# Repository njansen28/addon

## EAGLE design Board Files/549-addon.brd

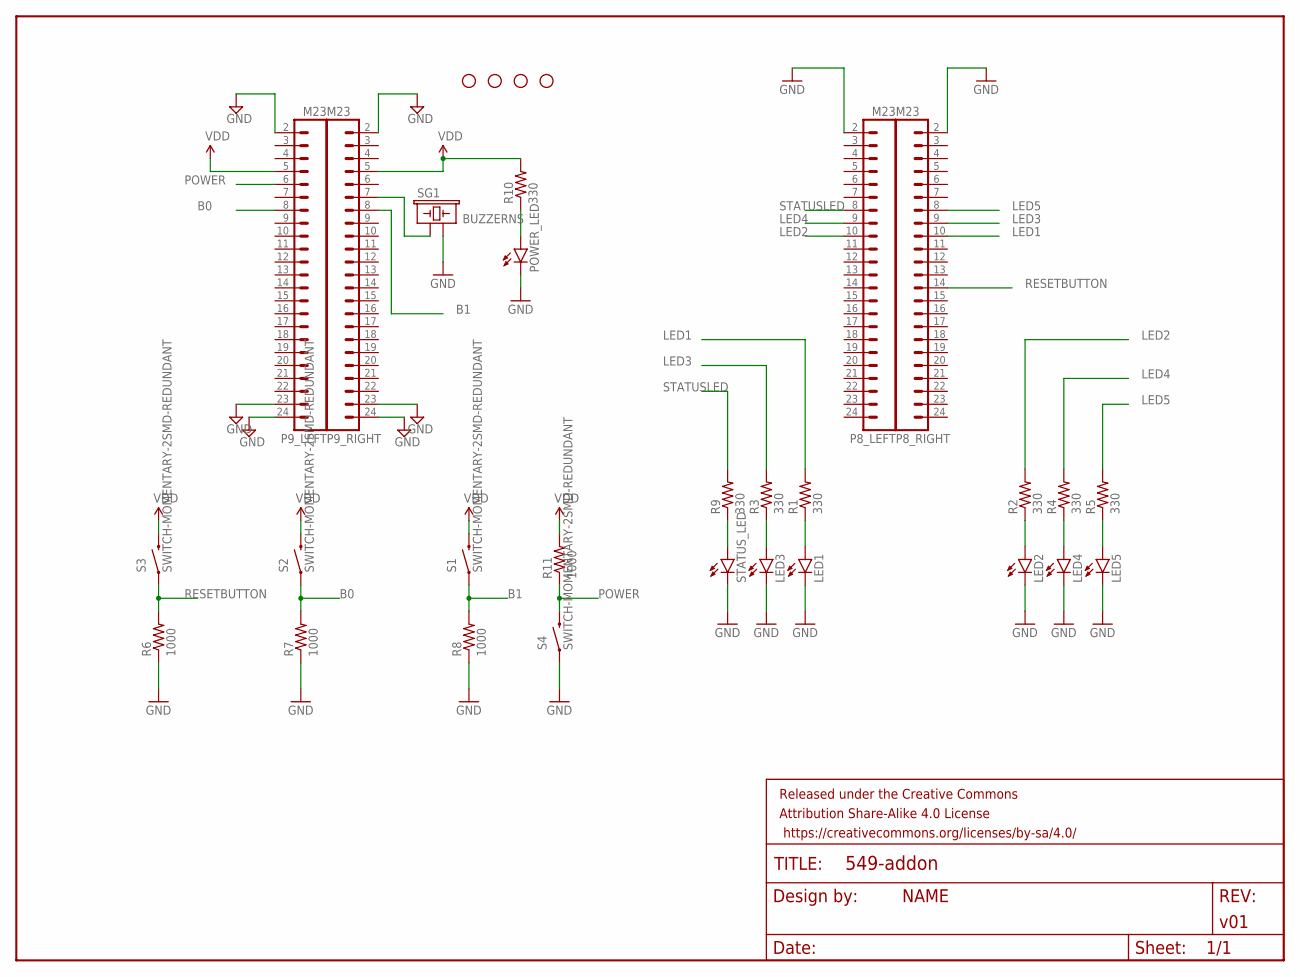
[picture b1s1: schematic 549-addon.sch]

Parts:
FRAME1: FRAME-LETTER; CREATIVE_COMMONS
LED1, LED2, LED3, LED4, LED5: LED1206; LED-1206
P8_LEFT, P8_RIGHT, P9_LEFT, P9_RIGHT: M23; 1X23
POWER_LED: LED1206; LED-1206
R1, R2, R3, R4, R5, R9, R10: 330; 1206
R6, R7, R8, R11: 1000; 1206
S1, S2, S3, S4: SWITCH-MOMENTARY-2SMD-REDUNDANT; TACTILE-SWITCH-SMD
SG1: BUZZERNS; BUZZER-12MM-NS
STANDOFF1, STANDOFF2, STANDOFF3, STANDOFF4: STAND-OFF
STATUS_LED: LED1206; LED-1206

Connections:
B0: P9_LEFT.8, R7.2, S2.1, S2.2 (1)
B1: P9_RIGHT.8, R8.2, S1.1, S1.2 (1)
GND: LED1.C, LED2.C, LED3.C, LED4.C, LED5.C, P8_LEFT.2, P8_RIGHT.2, P9_LEFT.2, P9_LEFT.23, P9_LEFT.24, P9_RIGHT.2, P9_RIGHT.23, P9_RIGHT.24, POWER_LED.C, R6.1, R7.1, R8.1, S4.1, S4.2 (1), SG1.- (2), STATUS_LED.C
LED1: P8_RIGHT.10, R1.2
LED2: P8_LEFT.10, R2.2
LED3: P8_RIGHT.9, R3.2
LED4: P8_LEFT.9, R4.2
LED5: P8_RIGHT.8, R5.2
unnamed: LED1.A, R1.1
unnamed: LED2.A, R2.1
unnamed: LED3.A, R3.1
unnamed: LED4.A, R4.1
unnamed: LED5.A, R5.1
unnamed: R9.1, STATUS_LED.A
unnamed: POWER_LED.A, R10.1
unnamed: P9_RIGHT.7, SG1.+ (1)
POWER: P9_LEFT.6, R11.1, S4.3 (2), S4.4 (2)
RESETBUTTON: P8_RIGHT.14, R6.2, S3.1, S3.2 (1)
STATUSLED: P8_LEFT.8, R9.2
VDD: P9_LEFT.5, P9_RIGHT.5, R10.2, R11.2, S1.3 (2), S1.4 (2), S2.3 (2), S2.4 (2), S3.3 (2), S3.4 (2)

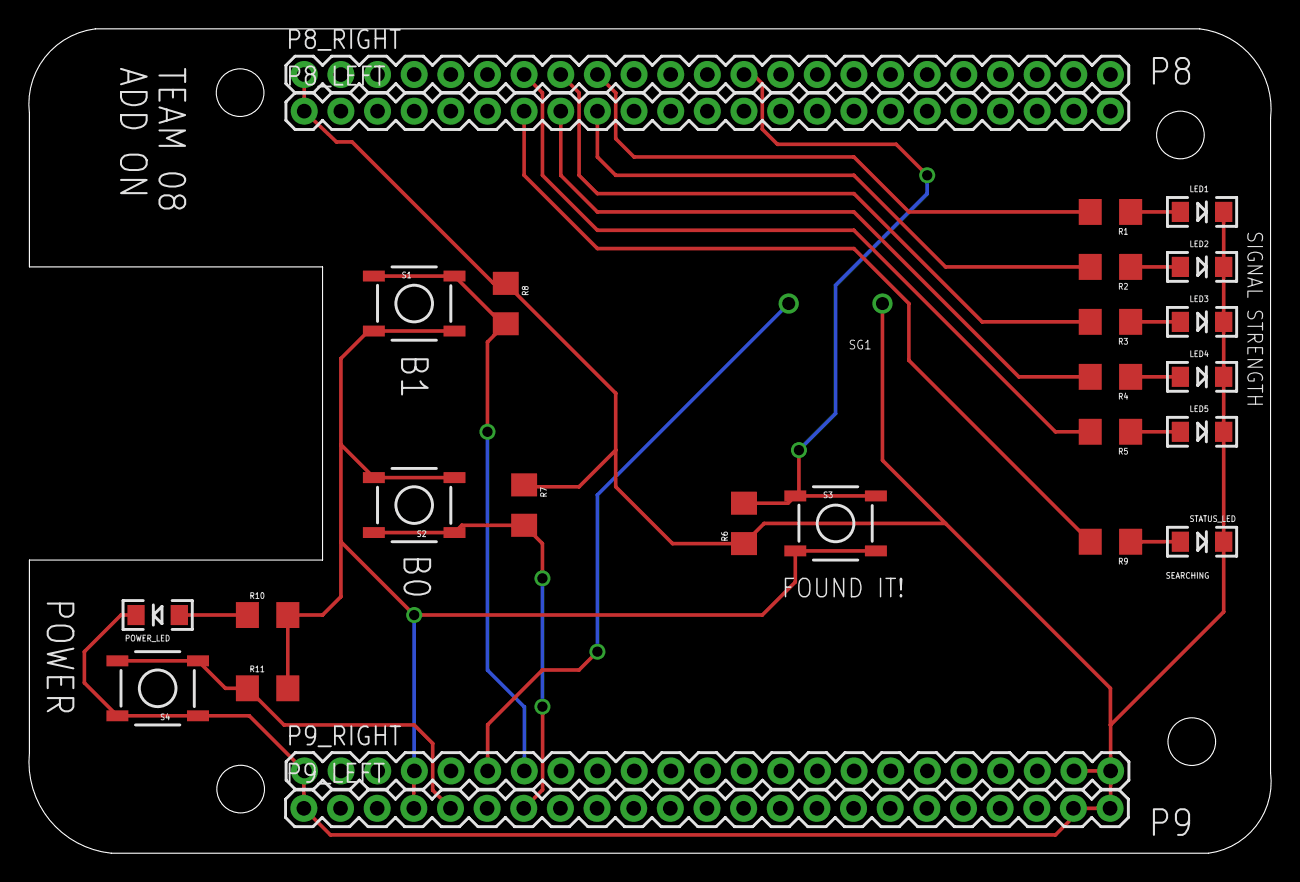
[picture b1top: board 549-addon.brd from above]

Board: 2 copper layers, 86.1 x 57.1 mm, 32 parts (0 on the bottom side), 20 nets.

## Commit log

2015-03-05 Initial commit of addon test code
2015-03-05 Added a folder for better organization
2015-03-16 Compiles, sends init sequence to BLE mini after button press, prints all bytes received from serial port (currently having issues with serial receive)
2015-03-21 brd and sch file for add on pcb. Please look over and make sure I'm not doing anything stupid
2015-03-22 Can you see this Bryan? If so, can you calm down a little bit? heh
2015-03-23 Modified some of Bryan's code to hopefully work for addon
2015-03-23 Fixed formatting for Brrrrrrryan (and python)
2015-03-23 added constants.py
2015-03-24 Added pin I/O. Removed worthless code. Runs on BBB. Not yet tested with beacon
2015-03-24 Also reorganized the repo a bit
2015-03-25 LED control works for signal strength (changed led pins). Able to receive a uuid to search for
2015-03-26 Updated schematic and layout to reflect changing pins for LEDs/buttons/buzzer
2015-03-30 Corrected pin I/O. Added status light code. Added reset button code
2015-04-01 addon scan: calibrated LED values run_addon.sh: Script to run addon_scan on startup. Must put in /etc/init.d/ Must have weird commented header thing then, run chmod 755 /etc/init/run_addon.sh Finally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
2015-04-01 Moved instructions for running program at startup to a file
2015-04-06 Added thread to monitor loss of signal. Also added the station's startup script
2015-04-08 Startup script for server and beacon_scanner. To get auto connect to wifi, use wicd-curses
2015-04-12 added LED/Buzzer test button
2015-04-13 fixed rssi value stuff
2015-04-26 rough draft of poster. No effort was put into lining up our pictures/names in case someone wants a different picture
2015-04-26 Adjusted pictures, changed architecture diagram to one with more detail
2015-04-27 Added QR code for webserver
2015-04-30 changed qr code to point to placeholder-ipupdater.com
2015-05-01 updated poster with Bryan/Arman feedback

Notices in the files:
parts and their libraries:
SparkFun-Aesthetics: Licensing: Creative Commons ShareAlike 4.0 International - https://creativecommons.org/licenses/by-sa/4.0
SparkFun-Aesthetics: Released under the Creative Commons Attribution Share-Alike 4.0 License
SparkFun-Aesthetics: https://creativecommons.org/licenses/by-sa/4.0
